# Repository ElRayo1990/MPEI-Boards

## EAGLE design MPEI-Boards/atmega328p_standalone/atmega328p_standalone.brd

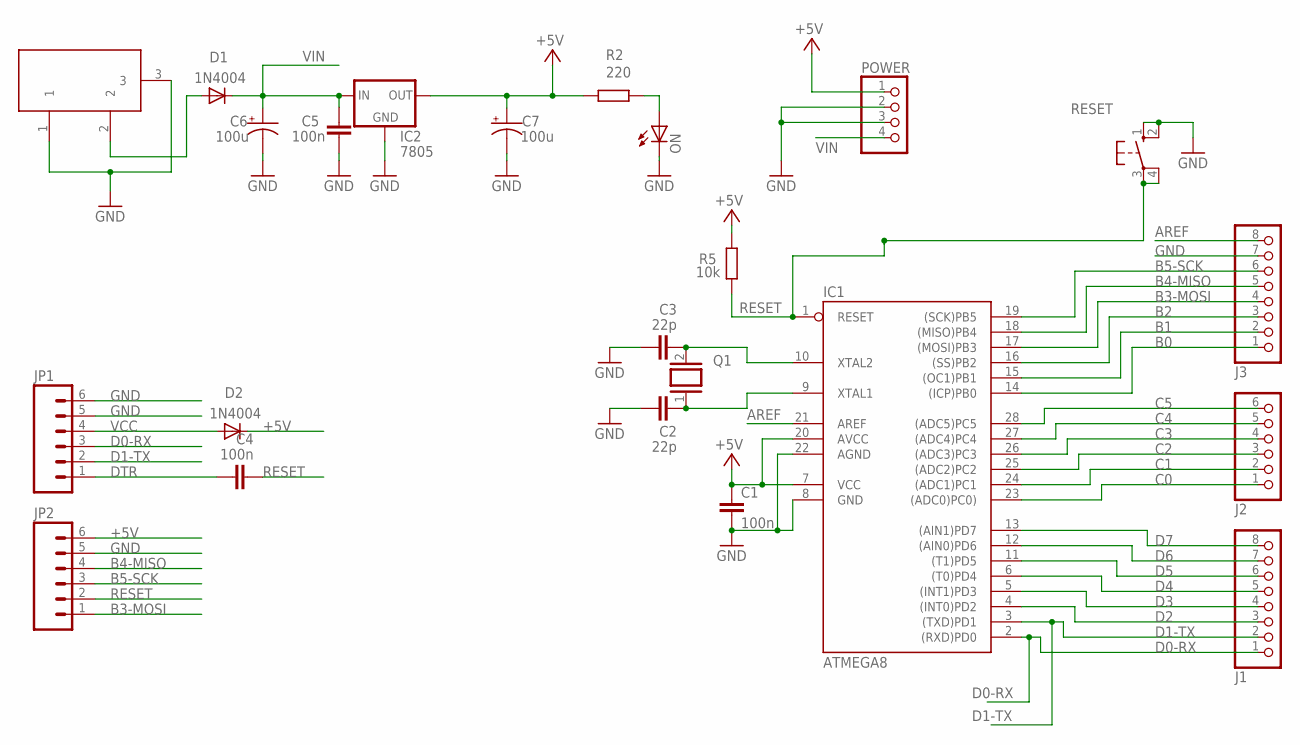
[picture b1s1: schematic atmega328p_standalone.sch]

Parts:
C1, C4, C5: 100n; C025-024X044
C2, C3: 22p; C025-024X044
C6, C7: 100u; E2,5-7
D1, D2: 1N4004; DO41-10
DC1: DC21MMX; DC-21MM
IC1: ATMEGA8; DIL28-3
IC2: 7805; 78MXXS
J1, J3: PINHD-1X8; 1X08
J2: PINHD-1X6; 1X06
JP1, JP2: M06SIP; 1X06
ON: LED3MM
POWER: PINHD-1X4; 1X04
Q1: XTAL/S; QS
R2: 220; 0207/10
R5: 10k; 0207/10
RESET: 10-XX; B3F-10XX

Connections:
+5V: C1.1, C7.+, D2.C, IC1.7 (VCC), IC1.20 (AVCC), IC2.OUT, JP2.6, POWER.1, R2.2, R5.2
AREF: IC1.21 (AREF), J3.8
B0: IC1.14 ((ICP)PB0), J3.1
B1: IC1.15 ((OC1)PB1), J3.2
B2: IC1.16 ((SS)PB2), J3.3
B3-MOSI: IC1.17 ((MOSI)PB3), J3.4, JP2.1
B4-MISO: IC1.18 ((MISO)PB4), J3.5, JP2.4
B5-SCK: IC1.19 ((SCK)PB5), J3.6, JP2.3
C0: IC1.23 ((ADC0)PC0)), J2.1
C1: IC1.24 ((ADC1)PC1), J2.2
C2: IC1.25 ((ADC2)PC2), J2.3
C3: IC1.26 ((ADC3)PC3), J2.4
C4: IC1.27 ((ADC4)PC4), J2.5
C5: IC1.28 ((ADC5)PC5), J2.6
D0-RX: IC1.2 ((RXD)PD0), J1.1, JP1.3
D1-TX: IC1.3 ((TXD)PD1), J1.2, JP1.2
D2: IC1.4 ((INT0)PD2), J1.3
D3: IC1.5 ((INT1)PD3), J1.4
D4: IC1.6 ((T0)PD4), J1.5
D5: IC1.11 ((T1)PD5), J1.6
D6: IC1.12 ((AIN0)PD6), J1.7
D7: IC1.13 ((AIN1)PD7), J1.8
DTR: C4.1, JP1.1
GND: C1.2, C2.1, C3.1, C5.1, C6.-, C7.-, DC1.1, DC1.3, IC1.8 (GND), IC1.22 (AGND), IC2.GND, J3.7, JP1.5, JP1.6, JP2.5, ON.K (C), POWER.2, POWER.3, RESET.1 (S), RESET.2 (S1)
unnamed: ON.A, R2.1
unnamed: C2.2, IC1.9 (XTAL1), Q1.1
unnamed: C3.2, IC1.10 (XTAL2), Q1.2
unnamed: D1.A, DC1.2
RESET: C4.2, IC1.1 (RESET), JP2.2, R5.1, RESET.3, RESET.4 (P1)
VCC: D2.A, JP1.4
VIN: C5.2, C6.+, D1.C, IC2.IN, POWER.4

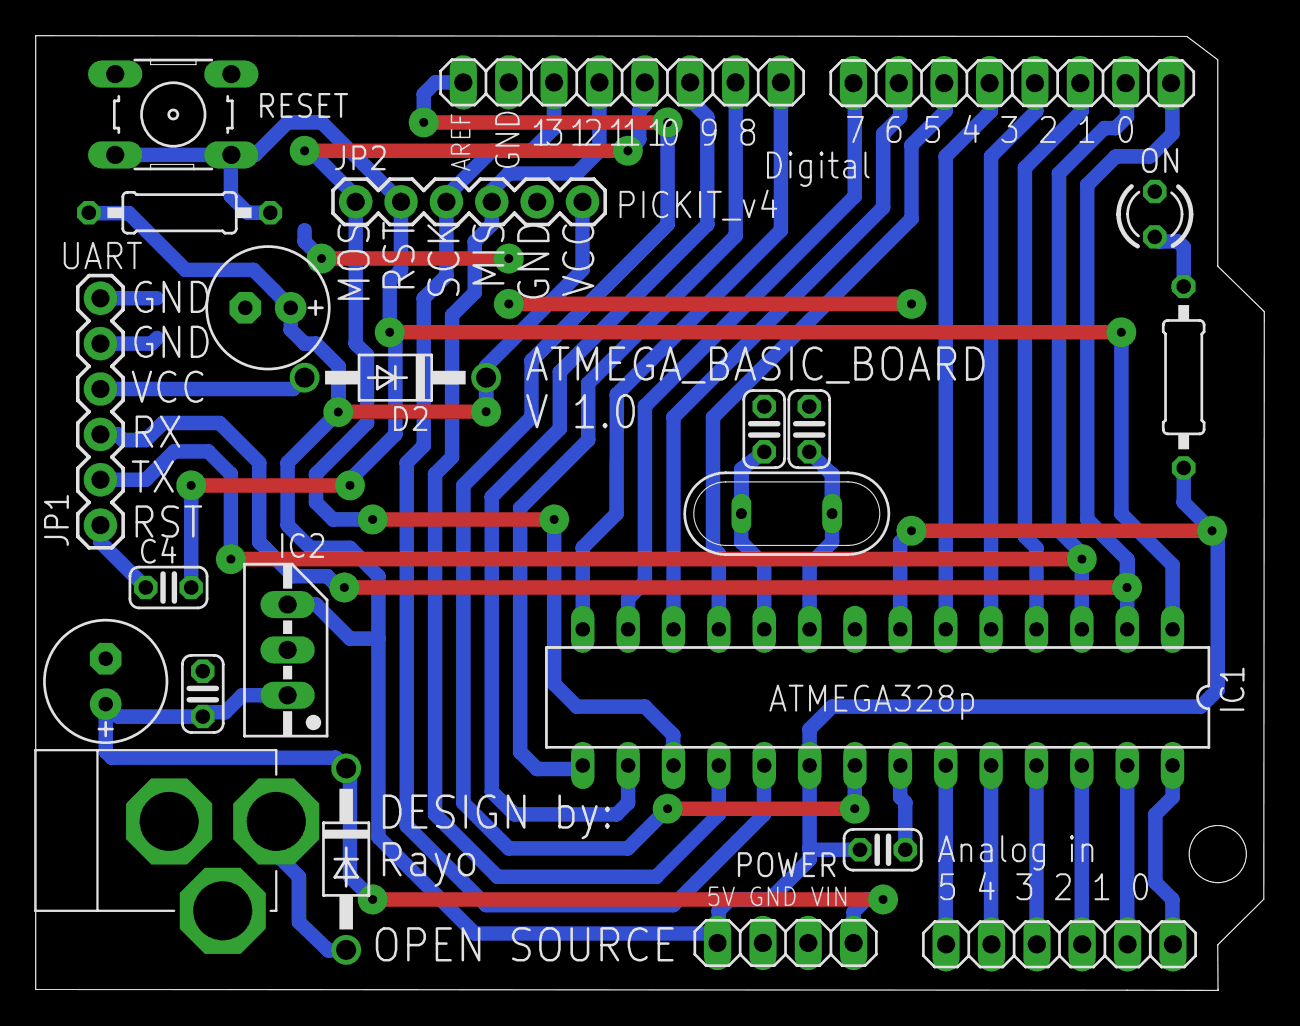
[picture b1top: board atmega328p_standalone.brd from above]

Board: 2 copper layers, 68.8 x 53.4 mm, 23 parts (0 on the bottom side), 31 nets.

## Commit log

2023-08-22 Update bords
2023-08-22 Update bords 2
2023-08-22 Update bords 4
2023-08-28 label verify
2023-08-31 add gerber files

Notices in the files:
parts and their libraries:
SparkFun: Licensing: CC v3.0 Share-Alike You are welcome to use this library for commercial purposes.
